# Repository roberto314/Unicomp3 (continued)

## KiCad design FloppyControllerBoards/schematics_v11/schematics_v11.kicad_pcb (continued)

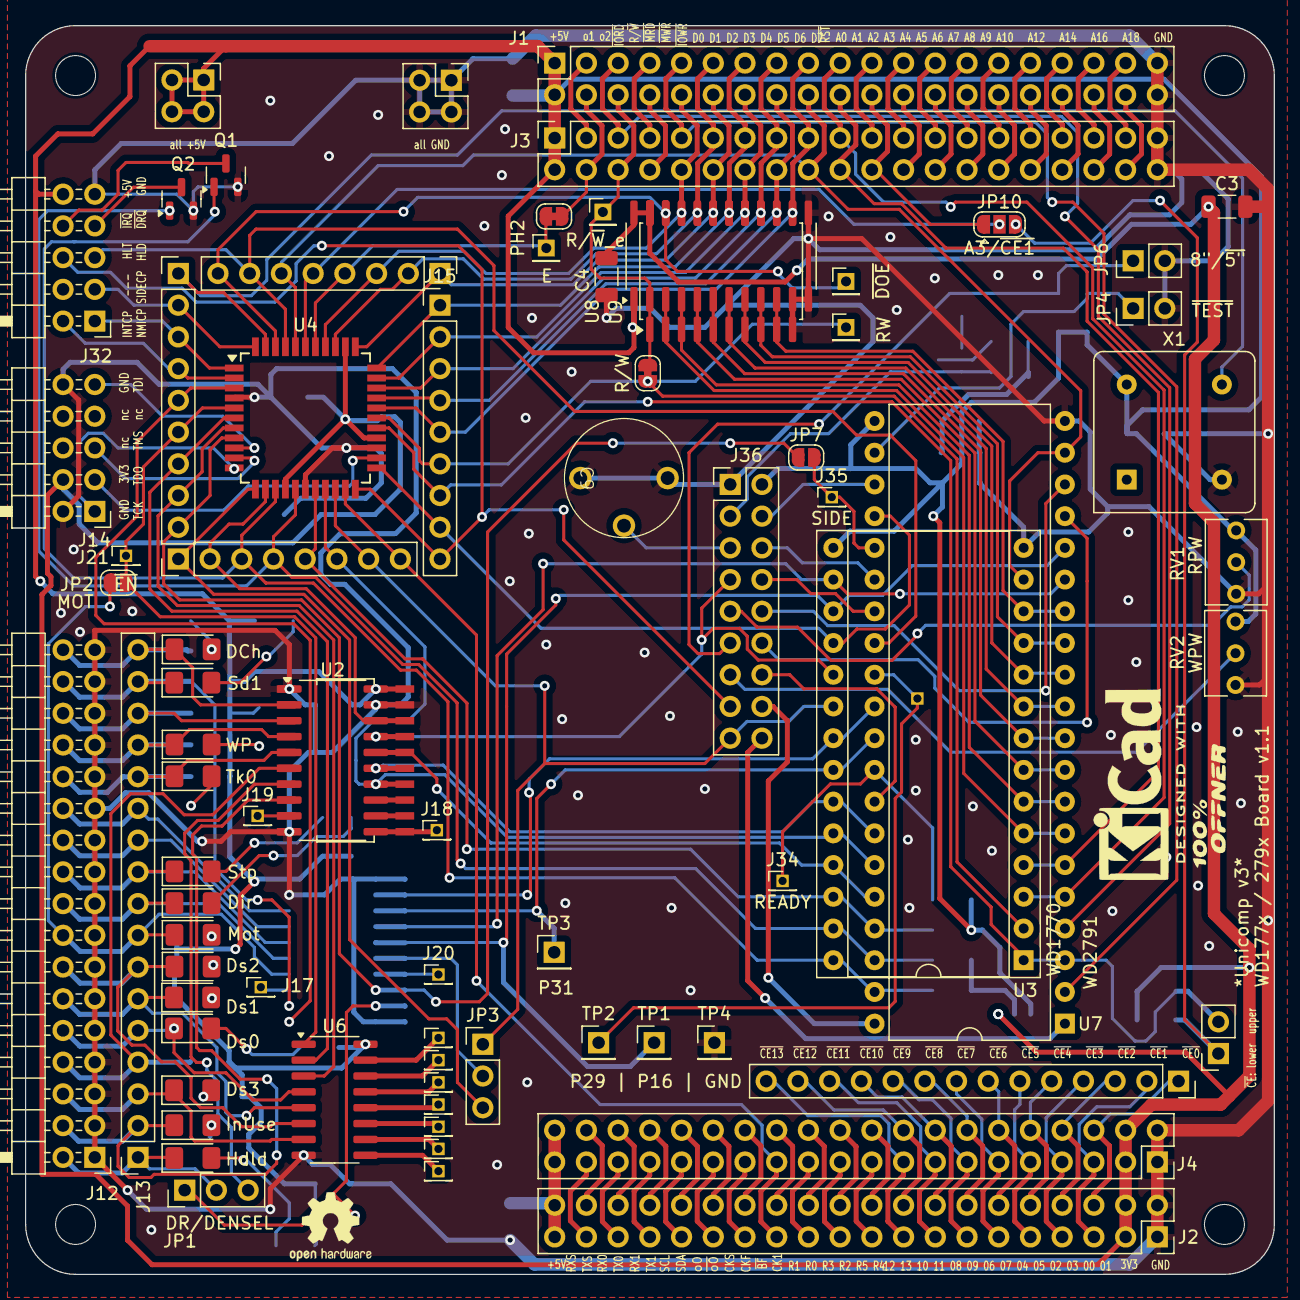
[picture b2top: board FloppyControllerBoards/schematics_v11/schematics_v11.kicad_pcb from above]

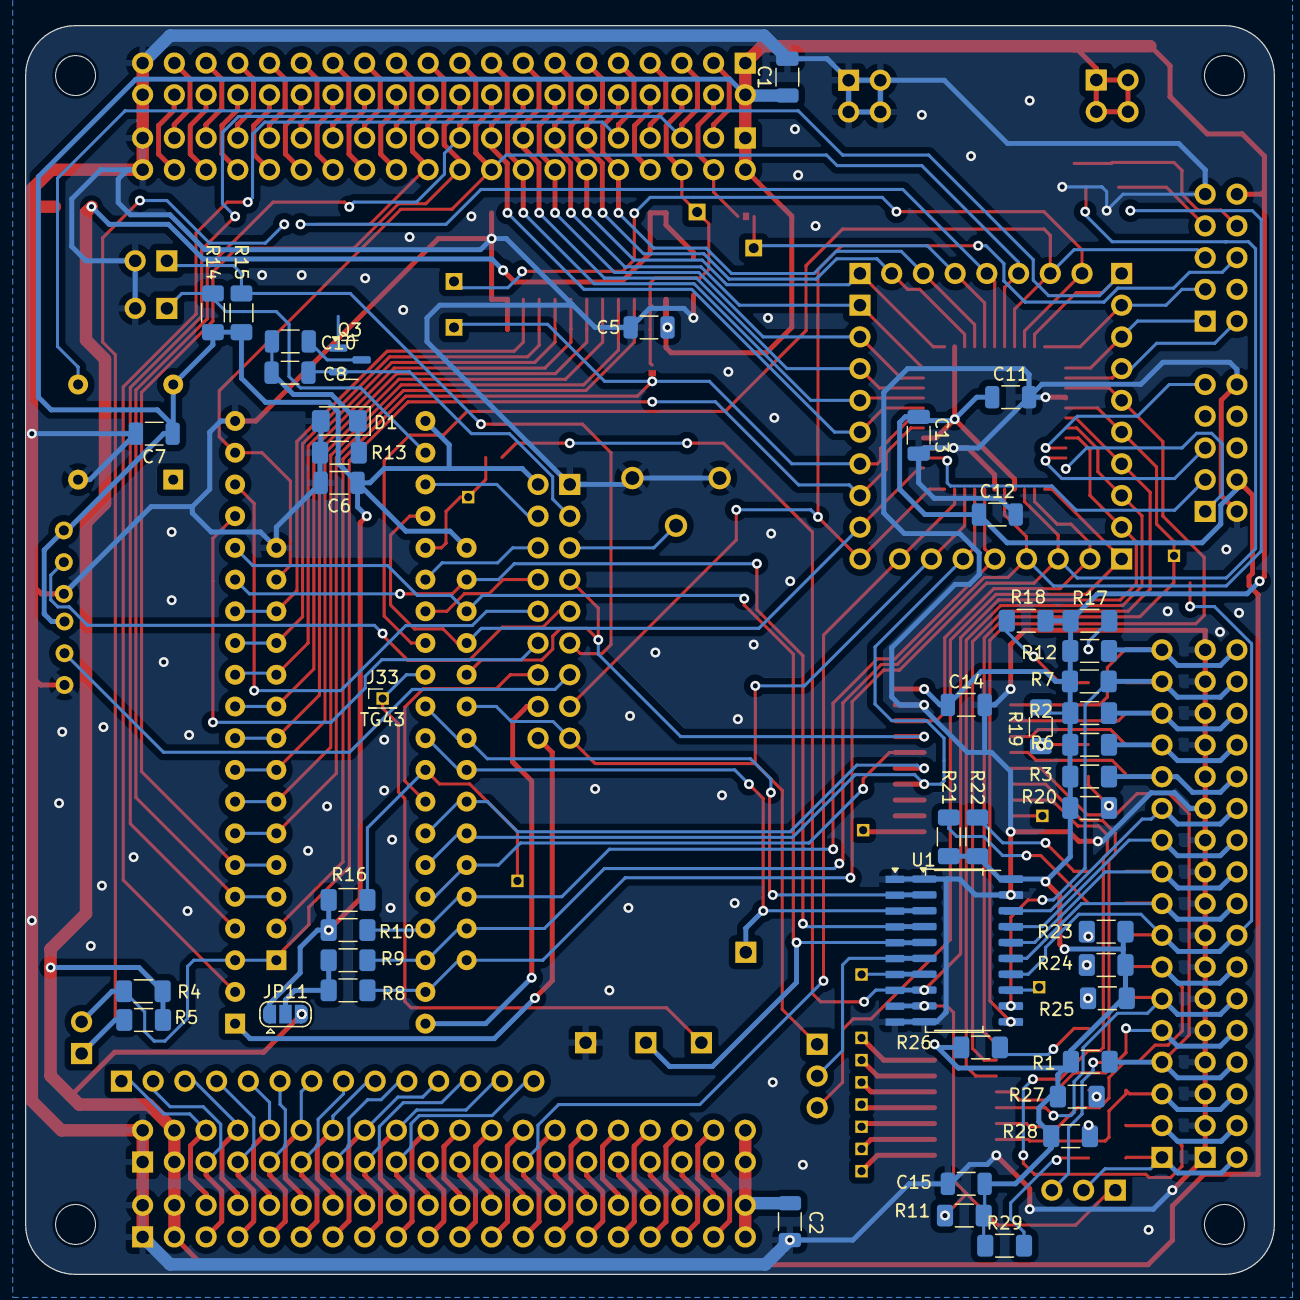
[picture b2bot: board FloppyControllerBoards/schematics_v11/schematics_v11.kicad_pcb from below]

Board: 2 copper layers, 100.0 x 100.0 mm, 130 parts (47 on the bottom side), 186 nets.

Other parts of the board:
J29: Conn_01x01; PinHeader_1x01_P1.27mm_Vertical

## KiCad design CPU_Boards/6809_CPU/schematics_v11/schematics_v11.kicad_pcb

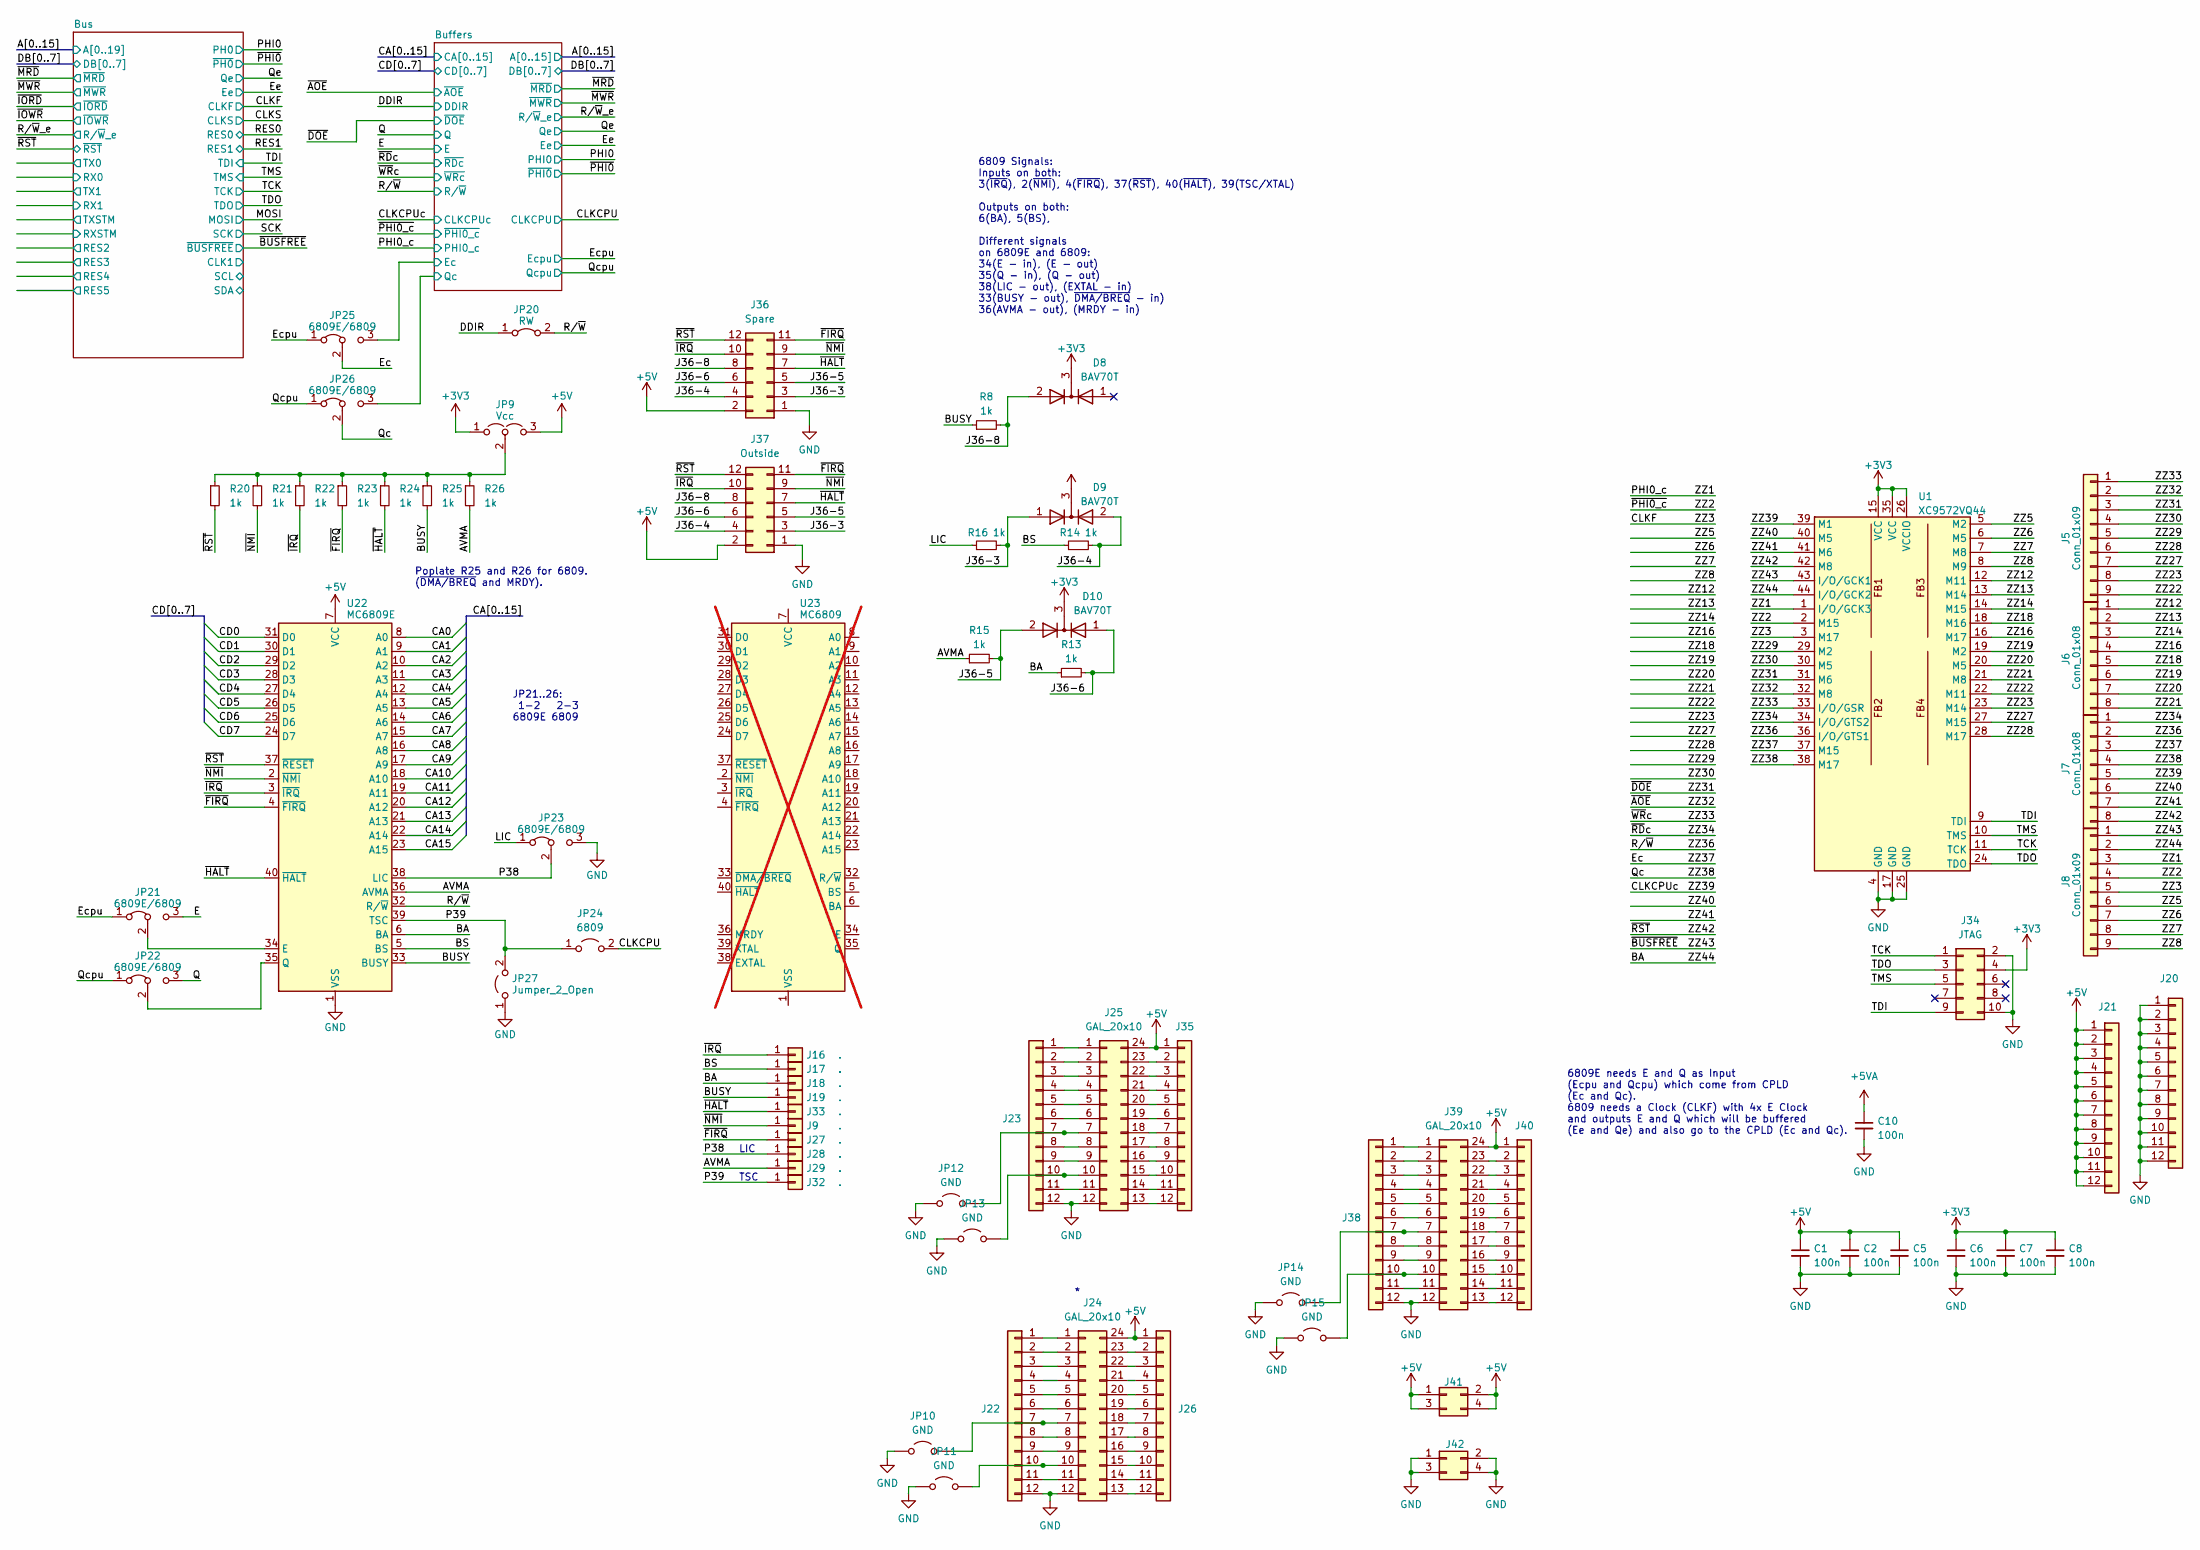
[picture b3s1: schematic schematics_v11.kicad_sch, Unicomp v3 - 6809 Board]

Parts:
C1, C2, C5, C6, C7, C8, C10: 100n; C_1206_3216Metric
D8, D9, D10: BAV70T; SOT-23_Handsoldering
J5, J8: Conn_01x09; PinHeader_1x09_P2.54mm_Vertical
J6, J7: Conn_01x08; PinHeader_1x08_P2.54mm_Vertical
J9, J16, J17, J18, J19, J27, J28, J29, J32, J33: .; PinHeader_1x01_P2.00mm_Vertical
J20, J21: Conn_01x12; PinHeader_1x12_P2.54mm_Vertical
J22, J23, J26, J35, J38, J40: Conn_01x12; PinSocket_1x12_P2.54mm_Vertical
J24, J25, J39: GAL_20x10; DIP-24_W7.62mm
J34: JTAG; PinHeader_2x05_P2.54mm_Horizontal
J36: Spare; PinHeader_2x06_P2.54mm_Vertical
J37: Outside; PinHeader_2x06_P2.54mm_Horizontal
J41, J42: Conn_02x02_Odd_Even; PinSocket_2x02_P2.54mm_Vertical
JP9: Vcc; SolderJumper-3_P1.3mm_Open_RoundedPad1.0x1.5mm_NumberLabels
JP10, JP11, JP12, JP13, JP14, JP15: GND; SolderJumper-2_P1.3mm_Open_RoundedPad1.0x1.5mm
JP20: RW; SolderJumper-2_P1.3mm_Bridged_RoundedPad1.0x1.5mm
JP21, JP22, JP23, JP25, JP26: 6809E/6809; SolderJumper-3_P1.3mm_Bridged12_RoundedPad1.0x1.5mm_NumberL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
JP24: 6809; SolderJumper-2_P1.3mm_Open_RoundedPad1.0x1.5mm
JP27: Jumper_2_Open; SolderJumper-2_P1.3mm_Open_RoundedPad1.0x1.5mm
R8, R13, R14, R15, R16, R20, R21, R22, R23, R24, R25, R26: 1k; R_1206_3216Metric_Pad1.30x1.75mm_HandSolder
U1: XC9572VQ44; TQFP-44_10x10mm_P0.8mm
U22: MC6809E; DIP-40_W15.24mm_LongPads
U23: MC6809; DIP-40_W15.24mm; not fitted

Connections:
+3V3: C6.1, C7.1, C8.1, D8.3 (K), D9.3 (K), D10.3 (K), J34.4, JP9.1 (A), U1.15 (VCC), U1.26 (VCCIO), U1.35 (VCC); also elsewhere on the board
+5V: C1.1, C2.1, C5.1, J21.1, J21.2, J21.3, J21.4, J21.5, J21.6, J21.7, J21.8, J21.9, J21.10, J21.11, J21.12, J24.24, J25.24, J26.1, J35.1, J36.2, J37.2, J39.24, J40.1, J41.1, J41.2, J41.3, J41.4, JP9.3 (B), U22.7 (VCC); also elsewhere on the board
+5VA: C10.1; also elsewhere on the board
/AVMA: J29.1, R15.1, R26.2, U22.36 (AVMA)
/BA: J8.2, J18.1, R13.1, U1.44 (I/O/GCK2), U22.6 (BA)
/BS: J17.1, R14.1, U22.5 (BS)
/BUSY: J19.1, R8.1, R25.2, U22.33 (BUSY)
/Buffers/Ec: JP25.3 (B); also elsewhere on the board
/Buffers/Qc: JP26.3 (B); also elsewhere on the board
/CA0: U22.8 (A0); also elsewhere on the board
/CA1: U22.9 (A1); also elsewhere on the board
/CA2: U22.10 (A2); also elsewhere on the board
/CA3: U22.11 (A3); also elsewhere on the board
/CA4: U22.12 (A4); also elsewhere on the board
/CA5: U22.13 (A5); also elsewhere on the board
/CA6: U22.14 (A6); also elsewhere on the board
/CA7: U22.15 (A7); also elsewhere on the board
/CA8: U22.16 (A8); also elsewhere on the board
/CA9: U22.17 (A9); also elsewhere on the board
/CA10: U22.18 (A10); also elsewhere on the board
/CA11: U22.19 (A11); also elsewhere on the board
/CA12: U22.20 (A12); also elsewhere on the board
/CA13: U22.21 (A13); also elsewhere on the board
/CA14: U22.22 (A14); also elsewhere on the board
/CA15: U22.23 (A15); also elsewhere on the board
/CD0: U22.31 (D0); also elsewhere on the board
/CD1: U22.30 (D1); also elsewhere on the board
/CD2: U22.29 (D2); also elsewhere on the board
/CD3: U22.28 (D3); also elsewhere on the board
/CD4: U22.27 (D4); also elsewhere on the board
/CD5: U22.26 (D5); also elsewhere on the board
/CD6: U22.25 (D6); also elsewhere on the board
/CD7: U22.24 (D7); also elsewhere on the board
/CLKCPU: JP24.2 (B); also elsewhere on the board
/CLKCPUc: J7.5, U1.39 (M1); also elsewhere on the board
/CLKF: J8.5, U1.3 (M17); also elsewhere on the board
/DDIR: JP20.1 (A); also elsewhere on the board
/E: JP21.3 (B); also elsewhere on the board
/Ec: J7.3, JP25.2 (C), U1.37 (M15)
/Ecpu: JP21.1 (A), JP25.1 (A); also elsewhere on the board
/J36-3: D9.1 (A), J36.3, J37.3, R16.2
/J36-4: D9.2 (A), J36.4, J37.4, R14.2
/J36-5: D10.2 (A), J36.5, J37.5, R15.2
/J36-6: D10.1 (A), J36.6, J37.6, R13.2
/J36-8: D8.2 (A), J36.8, J37.8, R8.2
/LIC: JP23.1 (A), R16.1
/P38: J28.1, JP23.2 (C), U22.38 (LIC)
/P39: J32.1, JP24.1 (A), JP27.2 (B), U22.39 (TSC)
/PHI0_c: J8.3, U1.1 (I/O/GCK3); also elsewhere on the board
/Q: JP22.3 (B); also elsewhere on the board
/Qc: J7.4, JP26.2 (C), U1.38 (M17)
/Qcpu: JP22.1 (A), JP26.1 (A); also elsewhere on the board
/R/~W: J7.2, JP20.2 (B), U1.36 (I/O/GTS1), U22.32 (R/~W); also elsewhere on the board
/TCK: J34.1, U1.11 (TCK)
/TDI: J34.9, U1.9 (TDI)
/TDO: J34.3, U1.24 (TDO)
/TMS: J34.5, U1.10 (TMS)
/ZZ2: J8.4, U1.2 (M15); also elsewhere on the board
/ZZ5: J8.6, U1.5 (M2)
/ZZ6: J8.7, U1.6 (M5)
/ZZ7: J8.8, U1.7 (M8)
/ZZ8: J8.9, U1.8 (M9)
/ZZ12: J6.1, U1.12 (M11)
/ZZ13: J6.2, U1.13 (M14)
/ZZ14: J6.3, U1.14 (M15)
/ZZ16: J6.4, U1.16 (M17)
/ZZ18: J6.5, U1.18 (M16)
/ZZ19: J6.6, U1.19 (M2)
/ZZ20: J6.7, U1.20 (M5)
/ZZ21: J6.8, U1.21 (M8)
/ZZ22: J5.9, U1.22 (M11)
/ZZ23: J5.8, U1.23 (M14)
/ZZ27: J5.7, U1.27 (M15)
/ZZ28: J5.6, U1.28 (M17)
/ZZ29: J5.5, U1.29 (M2)
/ZZ30: J5.4, U1.30 (M5)
/ZZ31: J5.3, U1.31 (M6); also elsewhere on the board
/ZZ32: J5.2, U1.32 (M8); also elsewhere on the board
/ZZ33: J5.1, U1.33 (I/O/GSR); also elsewhere on the board
/ZZ34: J7.1, U1.34 (I/O/GTS2); also elsewhere on the board
/ZZ40: J7.6, U1.40 (M5)
/ZZ41: J7.7, U1.41 (M6)
/ZZ42: J7.8, J36.12, J37.12, R20.2, U1.42 (M8), U22.37 (~RESET); also elsewhere on the board
/ZZ43: J8.1, U1.43 (I/O/GCK1); also elsewhere on the board
/~FIRQ: J27.1, J36.11, J37.11, R23.2, U22.4 (~FIRQ)
/~HALT: J33.1, J36.7, J37.7, R24.2, U22.40 (~HALT)
/~IRQ: J16.1, J36.10, J37.10, R22.2, U22.3 (~IRQ)
/~NMI: J9.1, J36.9, J37.9, R21.2, U22.2 (~NMI)
GND: C1.2, C2.2, C5.2, C6.2, C7.2, C8.2, C10.2, J20.1, J20.2, J20.3, J20.4, J20.5, J20.6, J20.7, J20.8, J20.9, J20.10, J20.11, J20.12, J22.12, J23.12, J24.12, J25.12, J34.2, J34.10, J36.1, J37.1, J38.12, J39.12, J42.1, J42.2, J42.3, J42.4, JP10.1 (A), JP11.1 (A), JP12.1 (A), JP13.1 (A), JP14.1 (A), JP15.1 (A), JP23.3 (B), JP27.1 (A), U1.4 (GND), U1.17 (GND), U1.25 (GND), U22.1 (VSS); also elsewhere on the board
unnamed: J22.1, J24.1
unnamed: J22.2, J24.2
unnamed: J22.3, J24.3
unnamed: J22.4, J24.4
unnamed: J22.5, J24.5
unnamed: J22.6, J24.6
unnamed: J22.7, J24.7, JP10.2 (B)
unnamed: J22.8, J24.8
unnamed: J22.9, J24.9
unnamed: J22.10, J24.10, JP11.2 (B)
unnamed: J22.11, J24.11
unnamed: J23.1, J25.1
unnamed: J23.2, J25.2
unnamed: J23.3, J25.3
unnamed: J23.4, J25.4
unnamed: J23.5, J25.5
unnamed: J23.6, J25.6
unnamed: J23.7, J25.7, JP12.2 (B)
unnamed: J23.8, J25.8
unnamed: J23.9, J25.9
unnamed: J23.10, J25.10, JP13.2 (B)
unnamed: J23.11, J25.11
unnamed: J24.13, J26.12
unnamed: J24.14, J26.11
unnamed: J24.15, J26.10
unnamed: J24.16, J26.9
unnamed: J24.17, J26.8
unnamed: J24.18, J26.7
unnamed: J24.19, J26.6
unnamed: J24.20, J26.5
unnamed: J24.21, J26.4
unnamed: J24.22, J26.3
unnamed: J24.23, J26.2
unnamed: J25.13, J35.12
unnamed: J25.14, J35.11
unnamed: J25.15, J35.10
unnamed: J25.16, J35.9
unnamed: J25.17, J35.8
unnamed: J25.18, J35.7
unnamed: J25.19, J35.6
unnamed: J25.20, J35.5
unnamed: J25.21, J35.4
unnamed: J25.22, J35.3
unnamed: J25.23, J35.2
unnamed: J38.1, J39.1
unnamed: J38.2, J39.2
unnamed: J38.3, J39.3
unnamed: J38.4, J39.4
unnamed: J38.5, J39.5
unnamed: J38.6, J39.6
unnamed: J38.7, J39.7, JP14.2 (B)
unnamed: J38.8, J39.8
unnamed: J38.9, J39.9
unnamed: J38.10, J39.10, JP15.2 (B)
unnamed: J38.11, J39.11
unnamed: J39.13, J40.12
unnamed: J39.14, J40.11
unnamed: J39.15, J40.10
unnamed: J39.16, J40.9
unnamed: J39.17, J40.8
unnamed: J39.18, J40.7
unnamed: J39.19, J40.6
unnamed: J39.20, J40.5
unnamed: J39.21, J40.4
unnamed: J39.22, J40.3
unnamed: J39.23, J40.2
unnamed: JP9.2 (C), R20.1, R21.1, R22.1, R23.1, R24.1, R25.1, R26.1
unnamed: JP21.2 (C), U22.34 (E)
unnamed: JP22.2 (C), U22.35 (Q)

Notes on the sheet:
Poplate R25 and R26 for 6809. (~{DMA/BREQ} and MRDY).
6809 Signals: Inputs on both: 3(~{IRQ}), 2(~{NMI}), 4(~{FIRQ}), 37(~{RST}), 40(~{HALT}), 39(TSC/XTAL) Outputs on both: 6(BA), 5(BS), Different signals on 6809E and 6809: 34(E - in), (E - out) 35(Q - in), (Q - out) 38(LIC - out), (EXTAL - in) 33(BUSY - out), ~{DMA/BREQ} - in) 36(AVMA - out), (MRDY -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
LIC
6809E needs E and Q as Input (Ecpu and Qcpu) which come from CPLD (Ec and Qc). 6809 needs a Clock (CLKF) with 4x E Clock and outputs E and Q which will be buffered (Ee and Qe) and also go to the CPLD (Ec and Qc).
TSC
JP21..26: 1-2 2-3 6809E 6809

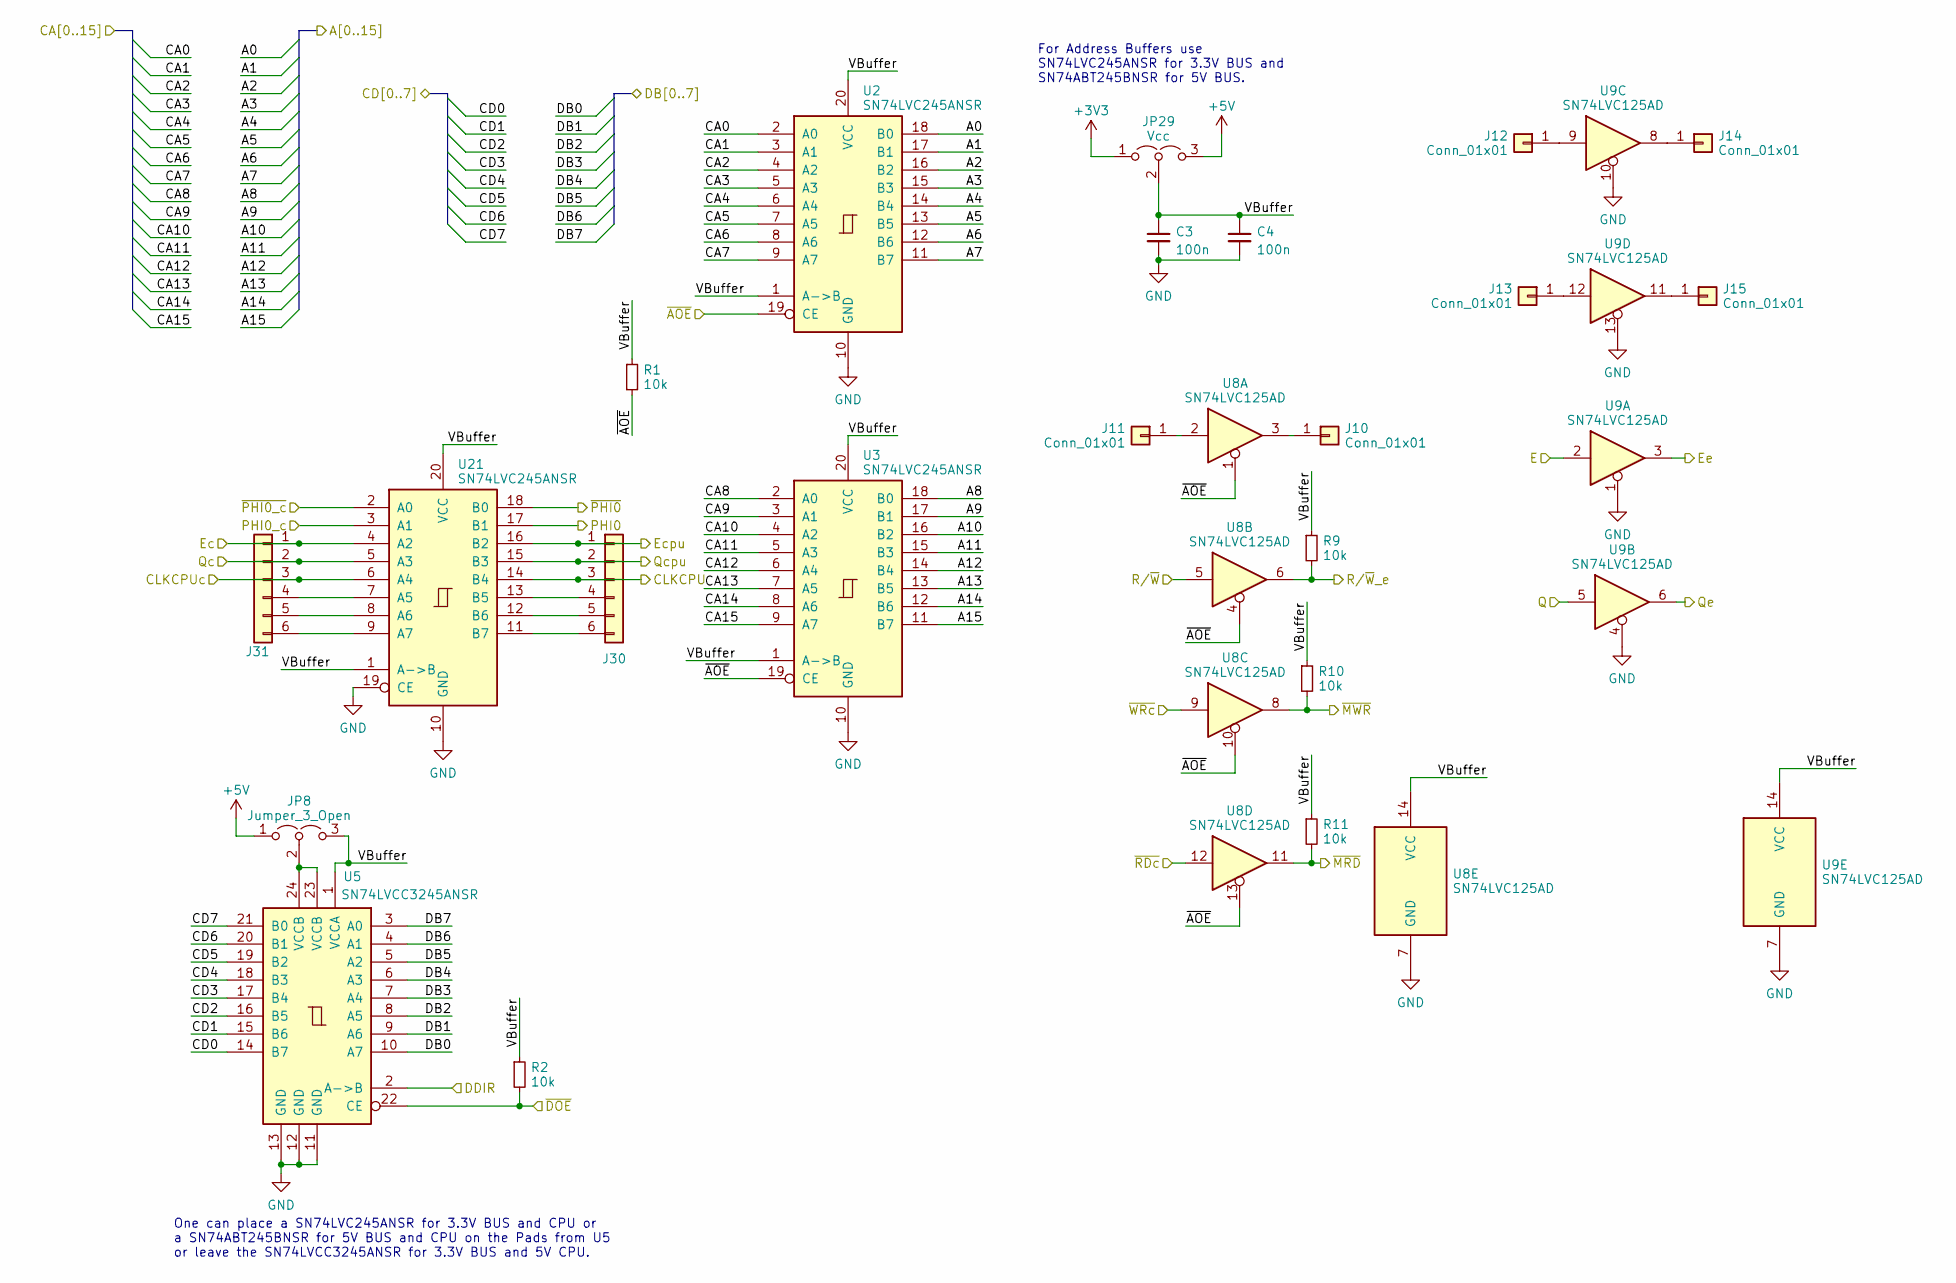
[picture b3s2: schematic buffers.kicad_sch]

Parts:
C3, C4: 100n; C_1206_3216Metric
J10, J11, J12, J13, J14, J15: Conn_01x01; PinHeader_1x01_P1.27mm_Vertical
J30, J31: Conn_01x06; PinHeader_1x06_P1.27mm_Vertical
JP8: Jumper_3_Open; SolderJumper-3_P1.3mm_Open_Pad1.0x1.5mm_NumberLabels
JP29: Vcc; SolderJumper-3_P1.3mm_Open_RoundedPad1.0x1.5mm_NumberLabels
R1, R2, R9, R10, R11: 10k; R_1206_3216Metric_Pad1.30x1.75mm_HandSolder
U2, U3, U21: SN74LVC245ANSR; SO-20_5.3x12.6mm_P1.27mm
U5: SN74LVCC3245ANSR; SO-24_5.3x15mm_P1.27mm
U8, U9: SN74LVC125AD; SOIC-14_3.9x8.7mm_P1.27mm

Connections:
+3V3: JP29.1 (A); also elsewhere on the board
+5V: JP8.1 (A), JP29.3 (B); also elsewhere on the board
/A0: U2.18 (B0); also elsewhere on the board
/A1: U2.17 (B1); also elsewhere on the board
/A2: U2.16 (B2); also elsewhere on the board
/A3: U2.15 (B3); also elsewhere on the board
/A4: U2.14 (B4); also elsewhere on the board
/A5: U2.13 (B5); also elsewhere on the board
/A6: U2.12 (B6); also elsewhere on the board
/A7: U2.11 (B7); also elsewhere on the board
/A8: U3.18 (B0); also elsewhere on the board
/A9: U3.17 (B1); also elsewhere on the board
/A10: U3.16 (B2); also elsewhere on the board
/A11: U3.15 (B3); also elsewhere on the board
/A12: U3.14 (B4); also elsewhere on the board
/A13: U3.13 (B5); also elsewhere on the board
/A14: U3.12 (B6); also elsewhere on the board
/A15: U3.11 (B7); also elsewhere on the board
/Buffers/Ec: J31.1, U21.4 (A2); also elsewhere on the board
/Buffers/Qc: J31.2, U21.5 (A3); also elsewhere on the board
/Buffers/VBuffer: C3.1, C4.1, JP8.3 (B), JP29.2 (C), R1.1, R2.1, R9.1, R10.1, R11.1, U2.1 (A->B), U2.20 (VCC), U3.1 (A->B), U3.20 (VCC), U5.1 (VCCA), U8.14 (VCC), U9.14 (VCC), U21.1 (A->B), U21.20 (VCC)
/CA0: U2.2 (A0); also elsewhere on the board
/CA1: U2.3 (A1); also elsewhere on the board
/CA2: U2.4 (A2); also elsewhere on the board
/CA3: U2.5 (A3); also elsewhere on the board
/CA4: U2.6 (A4); also elsewhere on the board
/CA5: U2.7 (A5); also elsewhere on the board
/CA6: U2.8 (A6); also elsewhere on the board
/CA7: U2.9 (A7); also elsewhere on the board
/CA8: U3.2 (A0); also elsewhere on the board
/CA9: U3.3 (A1); also elsewhere on the board
/CA10: U3.4 (A2); also elsewhere on the board
/CA11: U3.5 (A3); also elsewhere on the board
/CA12: U3.6 (A4); also elsewhere on the board
/CA13: U3.7 (A5); also elsewhere on the board
/CA14: U3.8 (A6); also elsewhere on the board
/CA15: U3.9 (A7); also elsewhere on the board
/CD0: U5.14 (B7); also elsewhere on the board
/CD1: U5.15 (B6); also elsewhere on the board
/CD2: U5.16 (B5); also elsewhere on the board
/CD3: U5.17 (B4); also elsewhere on the board
/CD4: U5.18 (B3); also elsewhere on the board
/CD5: U5.19 (B2); also elsewhere on the board
/CD6: U5.20 (B1); also elsewhere on the board
/CD7: U5.21 (B0); also elsewhere on the board
/CLKCPU: J30.3, U21.14 (B4); also elsewhere on the board
/CLKCPUc: J31.3, U21.6 (A4); also elsewhere on the board
/DB0: U5.10 (A7); also elsewhere on the board
/DB1: U5.9 (A6); also elsewhere on the board
/DB2: U5.8 (A5); also elsewhere on the board
/DB3: U5.7 (A4); also elsewhere on the board
/DB4: U5.6 (A3); also elsewhere on the board
/DB5: U5.5 (A2); also elsewhere on the board
/DB6: U5.4 (A1); also elsewhere on the board
/DB7: U5.3 (A0); also elsewhere on the board
/DDIR: U5.2 (A->B); also elsewhere on the board
/E: U9.2; also elsewhere on the board
/Ecpu: J30.1, U21.16 (B2); also elsewhere on the board
/Ee: U9.3; also elsewhere on the board
/PHI0: U21.17 (B1); also elsewhere on the board
/PHI0_c: U21.3 (A1); also elsewhere on the board
/Q: U9.5; also elsewhere on the board
/Qcpu: J30.2, U21.15 (B3); also elsewhere on the board
/Qe: U9.6; also elsewhere on the board
/R/~W: U8.5; also elsewhere on the board
/R/~W_e: R9.2, U8.6; also elsewhere on the board
/ZZ2: U21.2 (A0); also elsewhere on the board
/ZZ31: R2.2, U5.22 (CE); also elsewhere on the board
/ZZ32: R1.2, U2.19 (CE), U3.19 (CE), U8.1, U8.4, U8.10, U8.13; also elsewhere on the board
/ZZ33: U8.9; also elsewhere on the board
/ZZ34: U8.12; also elsewhere on the board
/~MRD: R11.2, U8.11; also elsewhere on the board
/~MWR: R10.2, U8.8; also elsewhere on the board
/~PHI0: U21.18 (B0); also elsewhere on the board
GND: C3.2, C4.2, U2.10 (GND), U3.10 (GND), U5.11 (GND), U5.12 (GND), U5.13 (GND), U8.7 (GND), U9.1, U9.4, U9.7 (GND), U9.10, U9.13, U21.10 (GND), U21.19 (CE); also elsewhere on the board
unnamed: J10.1, U8.3
unnamed: J11.1, U8.2
unnamed: J12.1, U9.9
unnamed: J13.1, U9.12
unnamed: J14.1, U9.8
unnamed: J15.1, U9.11
unnamed: J30.4, U21.13 (B5)
unnamed: J30.5, U21.12 (B6)
unnamed: J30.6, U21.11 (B7)
unnamed: J31.4, U21.7 (A5)
unnamed: J31.5, U21.8 (A6)
unnamed: J31.6, U21.9 (A7)
unnamed: JP8.2 (C), U5.23 (VCCB), U5.24 (VCCB)

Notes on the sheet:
One can place a SN74LVC245ANSR for 3.3V BUS and CPU or a SN74ABT245BNSR for 5V BUS and CPU on the Pads from U5 or leave the SN74LVCC3245ANSR for 3.3V BUS and 5V CPU.
For Address Buffers use SN74LVC245ANSR for 3.3V BUS and SN74ABT245BNSR for 5V BUS.

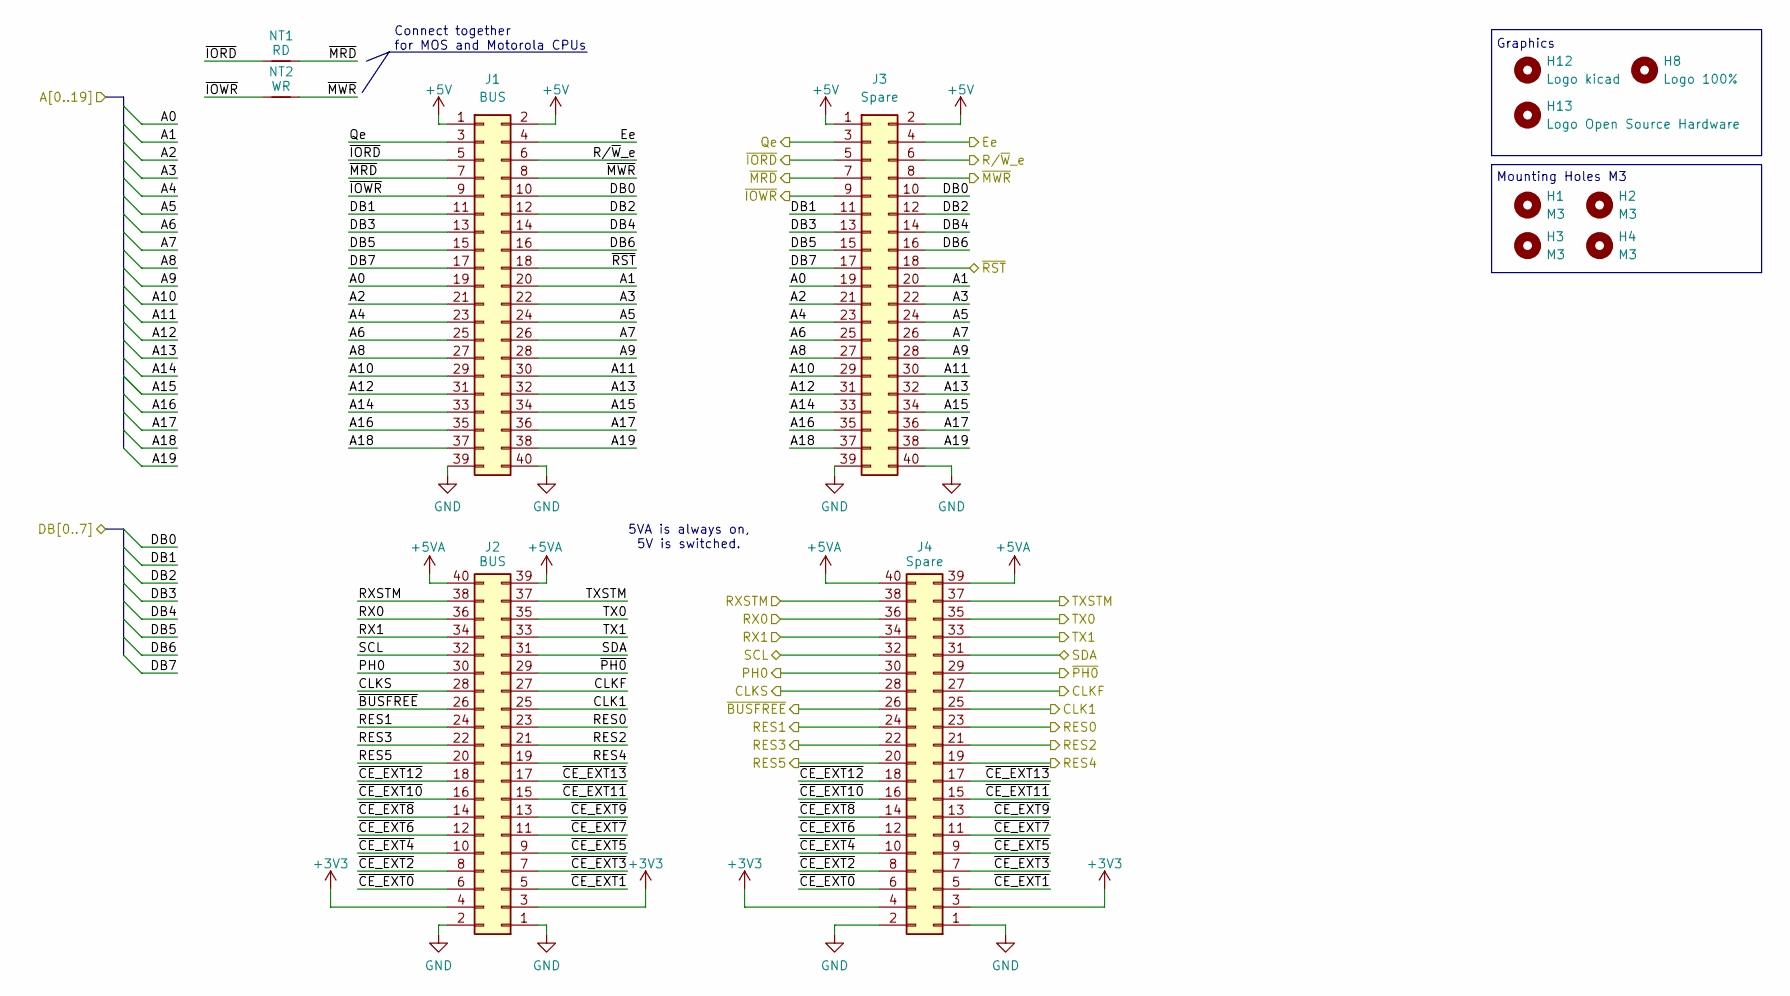
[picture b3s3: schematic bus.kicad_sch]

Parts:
H1, H2, H3, H4: M3; MountingHole_3.2mm_M3
H8: Logo 100%; Logo_100ProzentOffner_10x2.7mm
H12: Logo kicad; KiCad-Logo2_6mm_SilkScreen
H13: Logo Open Source Hardware; OSHW-Logo2_7.3x6mm_SilkScreen
J1, J2: BUS; PinSocket_2x20_P2.54mm_Vertical
J3, J4: Spare; PinSocket_2x20_P2.54mm_Vertical
NT1: RD; NetTie-2_SMD_Pad0.5mm
NT2: WR; NetTie-2_SMD_Pad0.5mm

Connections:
+3V3: J2.3, J2.4, J4.3, J4.4; also elsewhere on the board
+5V: J1.1, J1.2, J3.1, J3.2; also elsewhere on the board
+5VA: J2.39, J2.40, J4.39, J4.40; also elsewhere on the board
/A0: J1.19, J3.19; also elsewhere on the board
/A1: J1.20, J3.20; also elsewhere on the board
/A2: J1.21, J3.21; also elsewhere on the board
/A3: J1.22, J3.22; also elsewhere on the board
/A4: J1.23, J3.23; also elsewhere on the board
/A5: J1.24, J3.24; also elsewhere on the board
/A6: J1.25, J3.25; also elsewhere on the board
/A7: J1.26, J3.26; also elsewhere on the board
/A8: J1.27, J3.27; also elsewhere on the board
/A9: J1.28, J3.28; also elsewhere on the board
/A10: J1.29, J3.29; also elsewhere on the board
/A11: J1.30, J3.30; also elsewhere on the board
/A12: J1.31, J3.31; also elsewhere on the board
/A13: J1.32, J3.32; also elsewhere on the board
/A14: J1.33, J3.33; also elsewhere on the board
/A15: J1.34, J3.34; also elsewhere on the board
/Bus/A16: J1.35, J3.35
/Bus/A17: J1.36, J3.36
/Bus/A18: J1.37, J3.37
/Bus/A19: J1.38, J3.38
/Bus/CLK1: J2.25, J4.25
/Bus/RES2: J2.21, J4.21
/Bus/RES3: J2.22, J4.22
/Bus/RES4: J2.19, J4.19
/Bus/RES5: J2.20, J4.20
/Bus/RX0: J2.36, J4.36
/Bus/RX1: J2.34, J4.34
/Bus/RXSTM: J2.38, J4.38
/Bus/SCL: J2.32, J4.32
/Bus/SDA: J2.31, J4.31
/Bus/TX0: J2.35, J4.35
/Bus/TX1: J2.33, J4.33
/Bus/TXSTM: J2.37, J4.37
/Bus/~CE_EXT0: J2.6, J4.6
/Bus/~CE_EXT1: J2.5, J4.5
/Bus/~CE_EXT2: J2.8, J4.8
/Bus/~CE_EXT3: J2.7, J4.7
/Bus/~CE_EXT4: J2.10, J4.10
/Bus/~CE_EXT5: J2.9, J4.9
/Bus/~CE_EXT6: J2.12, J4.12
/Bus/~CE_EXT7: J2.11, J4.11
/Bus/~CE_EXT8: J2.14, J4.14
/Bus/~CE_EXT9: J2.13, J4.13
/Bus/~CE_EXT10: J2.16, J4.16
/Bus/~CE_EXT11: J2.15, J4.15
/Bus/~CE_EXT12: J2.18, J4.18
/Bus/~CE_EXT13: J2.17, J4.17
/CLKF: J2.27, J4.27; also elsewhere on the board
/CLKS: J2.28, J4.28
/DB0: J1.10, J3.10; also elsewhere on the board
/DB1: J1.11, J3.11; also elsewhere on the board
/DB2: J1.12, J3.12; also elsewhere on the board
/DB3: J1.13, J3.13; also elsewhere on the board
/DB4: J1.14, J3.14; also elsewhere on the board
/DB5: J1.15, J3.15; also elsewhere on the board
/DB6: J1.16, J3.16; also elsewhere on the board
/DB7: J1.17, J3.17; also elsewhere on the board
/Ee: J1.4, J3.4; also elsewhere on the board
/PHI0: J2.30, J4.30; also elsewhere on the board
/Qe: J1.3, J3.3; also elsewhere on the board
/RES0: J2.23, J4.23
/RES1: J2.24, J4.24
/R/~W_e: J1.6, J3.6; also elsewhere on the board
/ZZ42: J1.18, J3.18; also elsewhere on the board
/ZZ43: J2.26, J4.26; also elsewhere on the board
/~IORD: J1.5, J3.5, NT1.1
/~IOWR: J1.9, J3.9, NT2.1
/~MRD: J1.7, J3.7, NT1.2; also elsewhere on the board
/~MWR: J1.8, J3.8, NT2.2; also elsewhere on the board
/~PHI0: J2.29, J4.29; also elsewhere on the board
GND: J1.39, J1.40, J2.1, J2.2, J3.39, J3.40, J4.1, J4.2; also elsewhere on the board

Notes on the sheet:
5VA is always on, 5V is switched.
Graphics
Mounting Holes M3
Connect together for MOS and Motorola CPUs
